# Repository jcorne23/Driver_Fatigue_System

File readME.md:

# Driver Fatigue System

An integrated driver monitoring system using OpenCV and dlib on a Raspberry Pi to track fatigue through eye and mouth aspect ratios, calculating a running fatigue score based on blink and yawn patterns. The ESP32-CAM streams live video over a custom webserver and displays real-time fatigue data via OLED. An onboard MQ3 sensor supports alcohol detection through a guided breathalyzer test, calibrated using controlled samples and baseline readings. A Flask server coordinates system behavior and enables mobile-based interaction, including optional emergency alert triggers—no internet required. Each respective folder has the code associated with each device with the inclusion of schematics and PCB files. Made and designed by Julio Cornejo and Vincent Ng. 

- [Design Document (PDF)](docs/design_document.pdf)
- [Engineering Notebook](docs/engineering_notebook.md)
- [Final Paper (PDF)](docs/final_report.pdf)

                                                Click the thumbnail to watch the demo!

- [Video Demo 2](https://drive.google.com/file/d/1_dD5bf3DfNFZJkOF3wCcVmGohEKaDvxr/view?usp=sharing)

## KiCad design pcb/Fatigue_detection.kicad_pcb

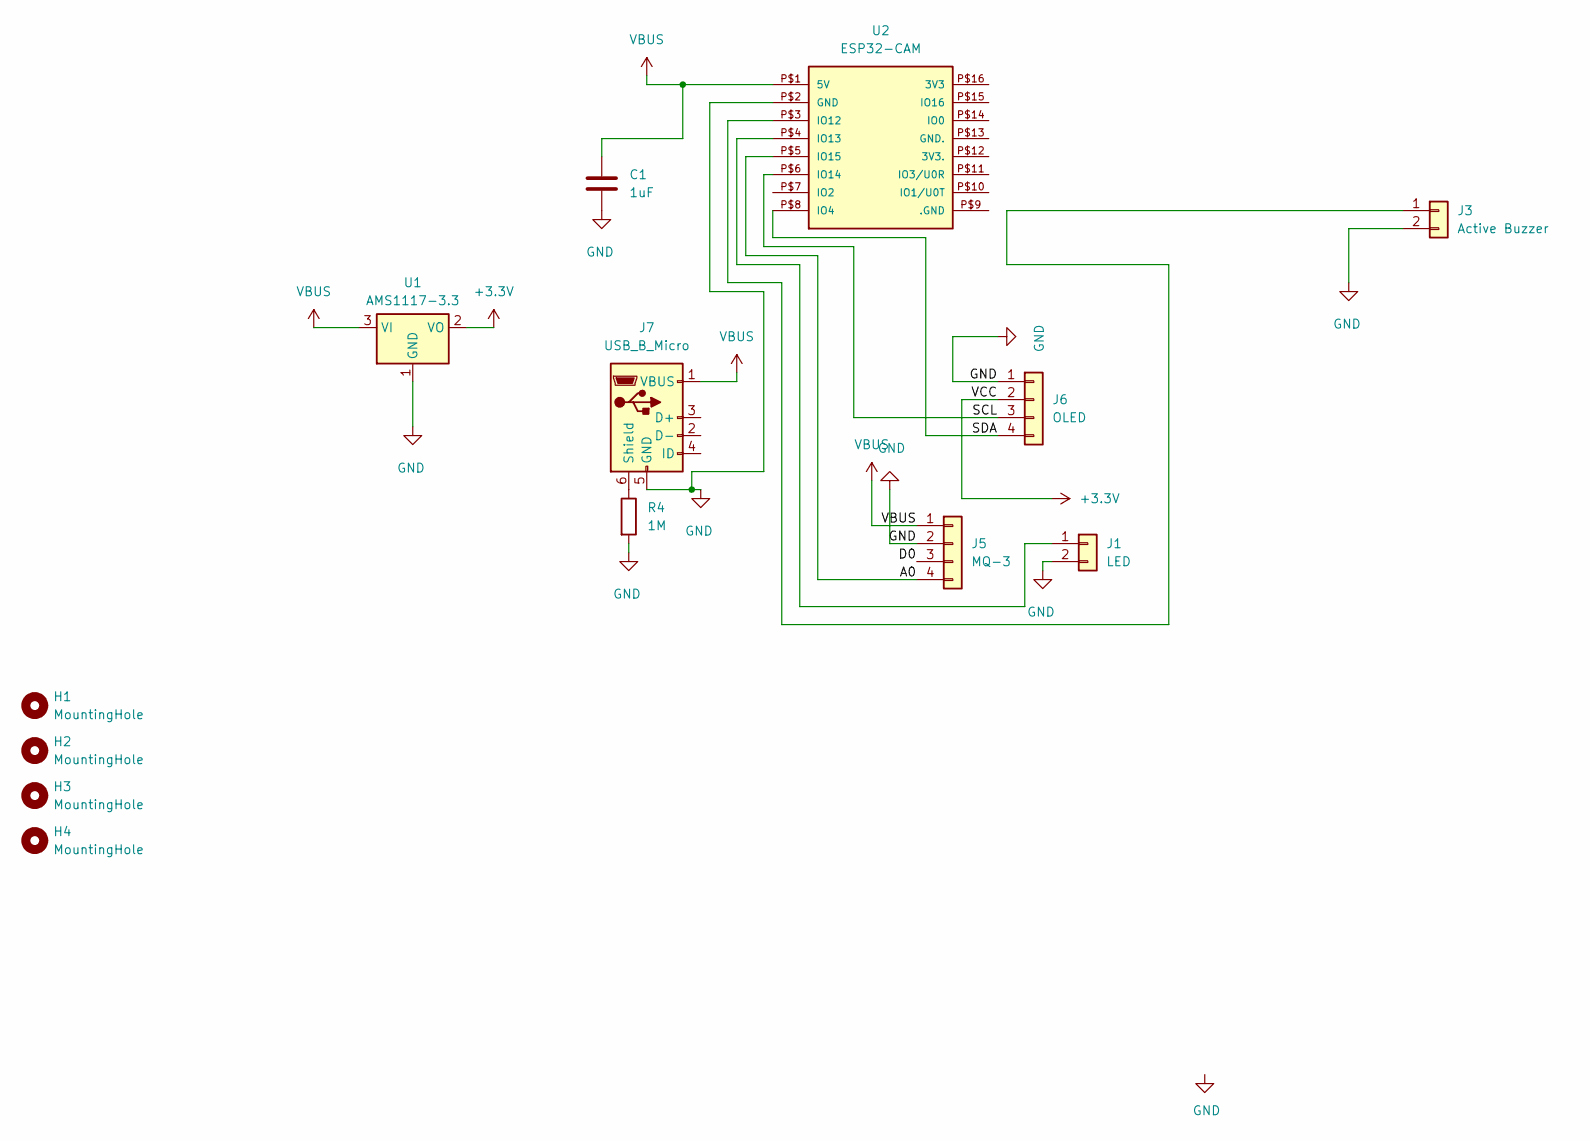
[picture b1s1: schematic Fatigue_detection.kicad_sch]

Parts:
C1: 1uF; C_0805_2012Metric_Pad1.18x1.45mm_HandSolder
H1, H2, H3, H4: MountingHole; MountingHole_3.2mm_M3
J1: LED; Molex_KK-254_AE-6410-02A_1x02_P2.54mm_Vertical
J3: Active Buzzer; Molex_KK-254_AE-6410-02A_1x02_P2.54mm_Vertical
J5: MQ-3; Molex_KK-254_AE-6410-04A_1x04_P2.54mm_Vertical
J6: OLED; Molex_KK-254_AE-6410-04A_1x04_P2.54mm_Vertical
J7: USB_B_Micro; USB_Micro-B_Amphenol_10118194-0001LF_Horizontal
R4: 1M; R_0805_2012Metric_Pad1.20x1.40mm_HandSolder
U1: AMS1117-3.3; SOT-223-3_TabPin2
U2: ESP32-CAM

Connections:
+3.3V: J6.2, U1.2 (VO)
/A0: J5.4, U2.P$5 (IO15)
/D0: J5.3
/SCL: J6.3, U2.P$6 (IO14)
/SDA: J6.4, U2.P$8 (IO4)
GND: C1.2, J1.2, J3.2, J5.2, J6.1, J7.5 (GND), R4.2, U1.1 (GND), U2.P$2 (GND); also elsewhere on the board
unnamed: J1.1, U2.P$4 (IO13)
unnamed: J3.1, U2.P$3 (IO12)
unnamed 8: J7.6 (Shield), R4.1; also elsewhere on the board
VBUS: C1.1, J5.1, J7.1 (VBUS), U1.3 (VI), U2.P$1 (5V); also elsewhere on the board

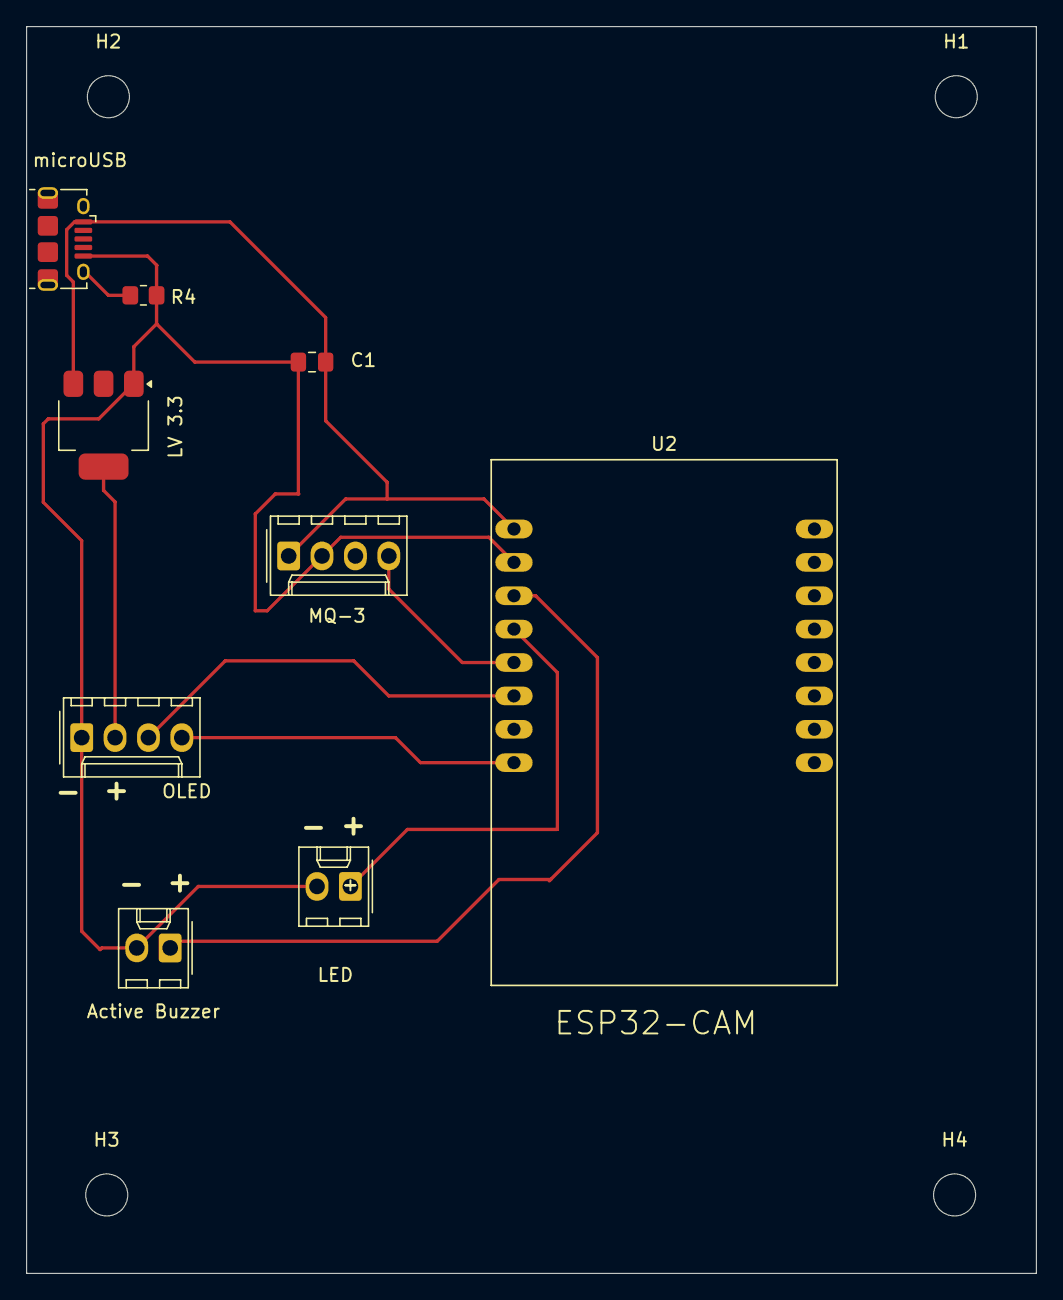
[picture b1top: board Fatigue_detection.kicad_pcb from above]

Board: 2 copper layers, 76.8 x 94.9 mm, 13 parts (0 on the bottom side), 9 nets.

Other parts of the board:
microUSB: USB_B_Micro; USB_Micro-B_Amphenol_10118194-0001LF_Horizontal

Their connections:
GND: microUSB.5 (GND); also elsewhere on the board
unnamed 8: microUSB.6 (Shield); also elsewhere on the board
VBUS: microUSB.1 (VBUS); also elsewhere on the board

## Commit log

2025-05-13 Create hi
2025-05-13 Upload Engineering Notebook
2025-05-13 Uploaded Engineering Notebook
2025-05-13 Add Design Document
2025-05-13 pi uploading files
2025-05-13 Uploading ARDUINO IDE ESP FILES
2025-05-13 PCB files
